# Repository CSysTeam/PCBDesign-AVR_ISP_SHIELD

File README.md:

# PCBDesign-AVR_ISP_SHIELD
A shield used to burn bootloader or program another ATMEGA329P IC.

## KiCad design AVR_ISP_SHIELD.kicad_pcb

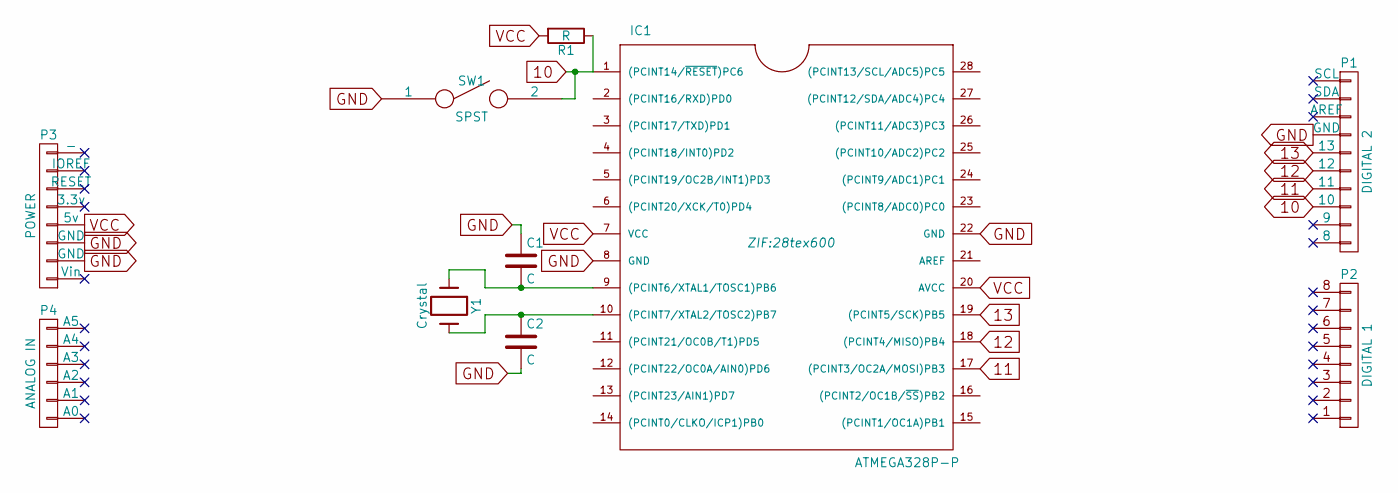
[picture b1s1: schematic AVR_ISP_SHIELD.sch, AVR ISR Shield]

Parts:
C1, C2: C; C_Disc_D3_P2.5
IC1: ATMEGA328P-P; 28tex600
P1: DIGITAL 2; Pin_Header_Straight_1x10
P2: DIGITAL 1; Pin_Header_Straight_1x08
P3: POWER; Pin_Header_Straight_1x08
P4: ANALOG IN; Pin_Header_Straight_1x06
R1: R; Resistor_Horizontal_RM10mm
SW1: SPST; SW_PUSH_SMALL
Y1: Crystal; Crystal_HC49-U_Vertical

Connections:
10: IC1.1 ((PCINT14/~RESET~)PC6), P1.3 (10), R1.1, SW1.2
11: IC1.17 ((PCINT3/OC2A/MOSI)PB3), P1.4 (11)
12: IC1.18 ((PCINT4/MISO)PB4), P1.5 (12)
13: IC1.19 ((PCINT5/SCK)PB5), P1.6 (13)
GND: C1.1, C2.2, IC1.8 (GND), IC1.22 (GND), P1.7 (GND), P3.2 (GND), P3.3 (GND), SW1.1
unnamed: C1.2, IC1.9 ((PCINT6/XTAL1/TOSC1)PB6), Y1.1
unnamed: C2.1, IC1.10 ((PCINT7/XTAL2/TOSC2)PB7), Y1.2
VCC: IC1.7 (VCC), IC1.20 (AVCC), P3.4 (5v), R1.2

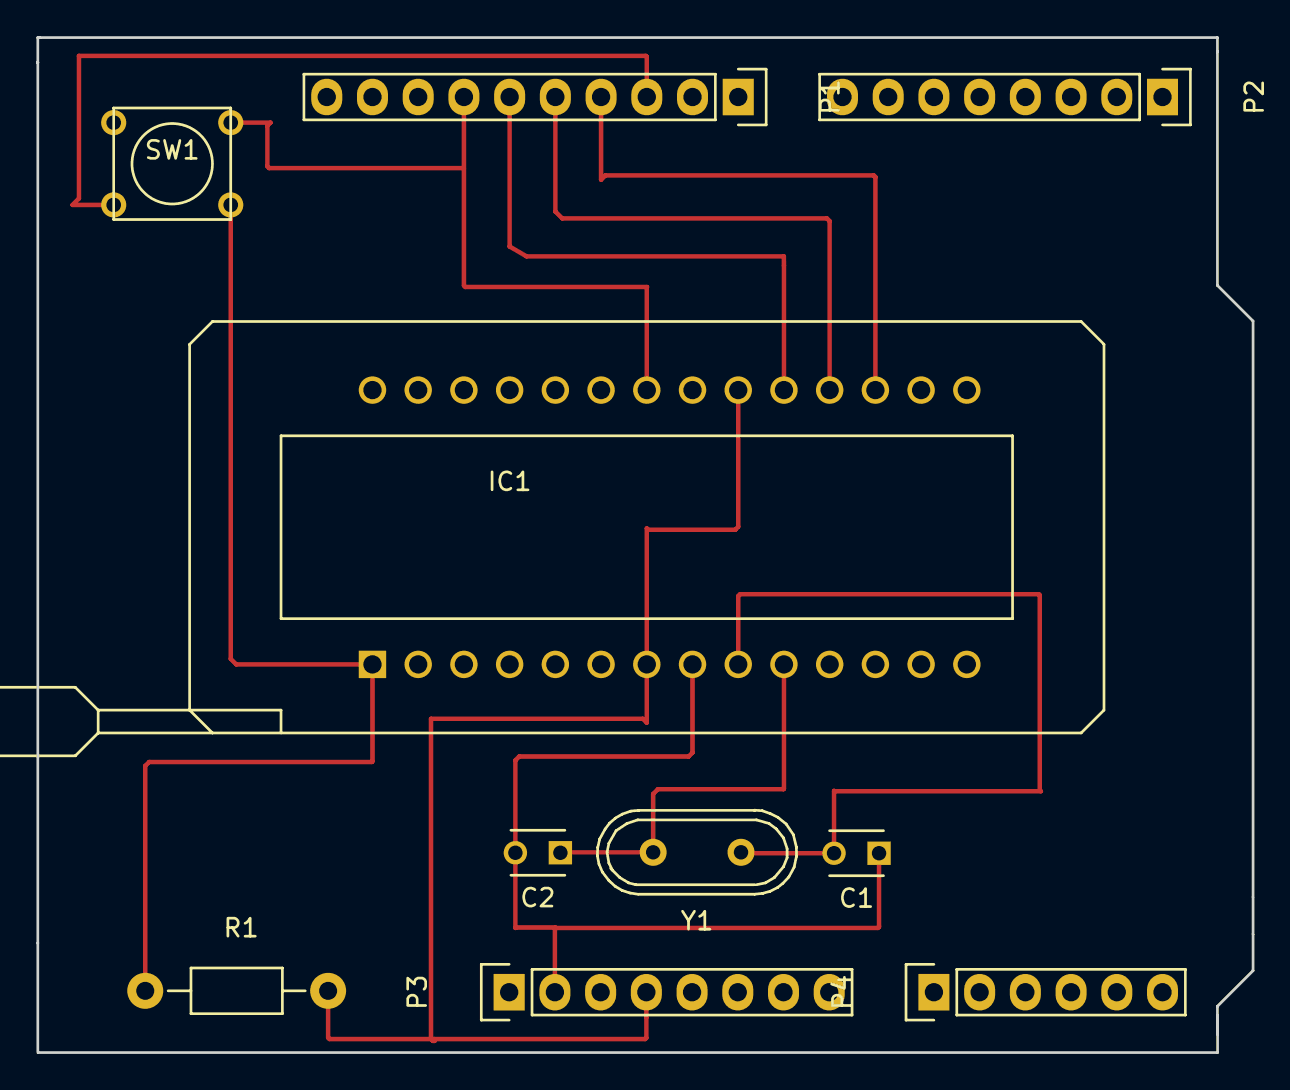
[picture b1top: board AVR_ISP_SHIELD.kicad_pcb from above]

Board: 2 copper layers, 67.5 x 56.4 mm, 10 parts (0 on the bottom side), 8 nets.

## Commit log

2016-08-23 final design
